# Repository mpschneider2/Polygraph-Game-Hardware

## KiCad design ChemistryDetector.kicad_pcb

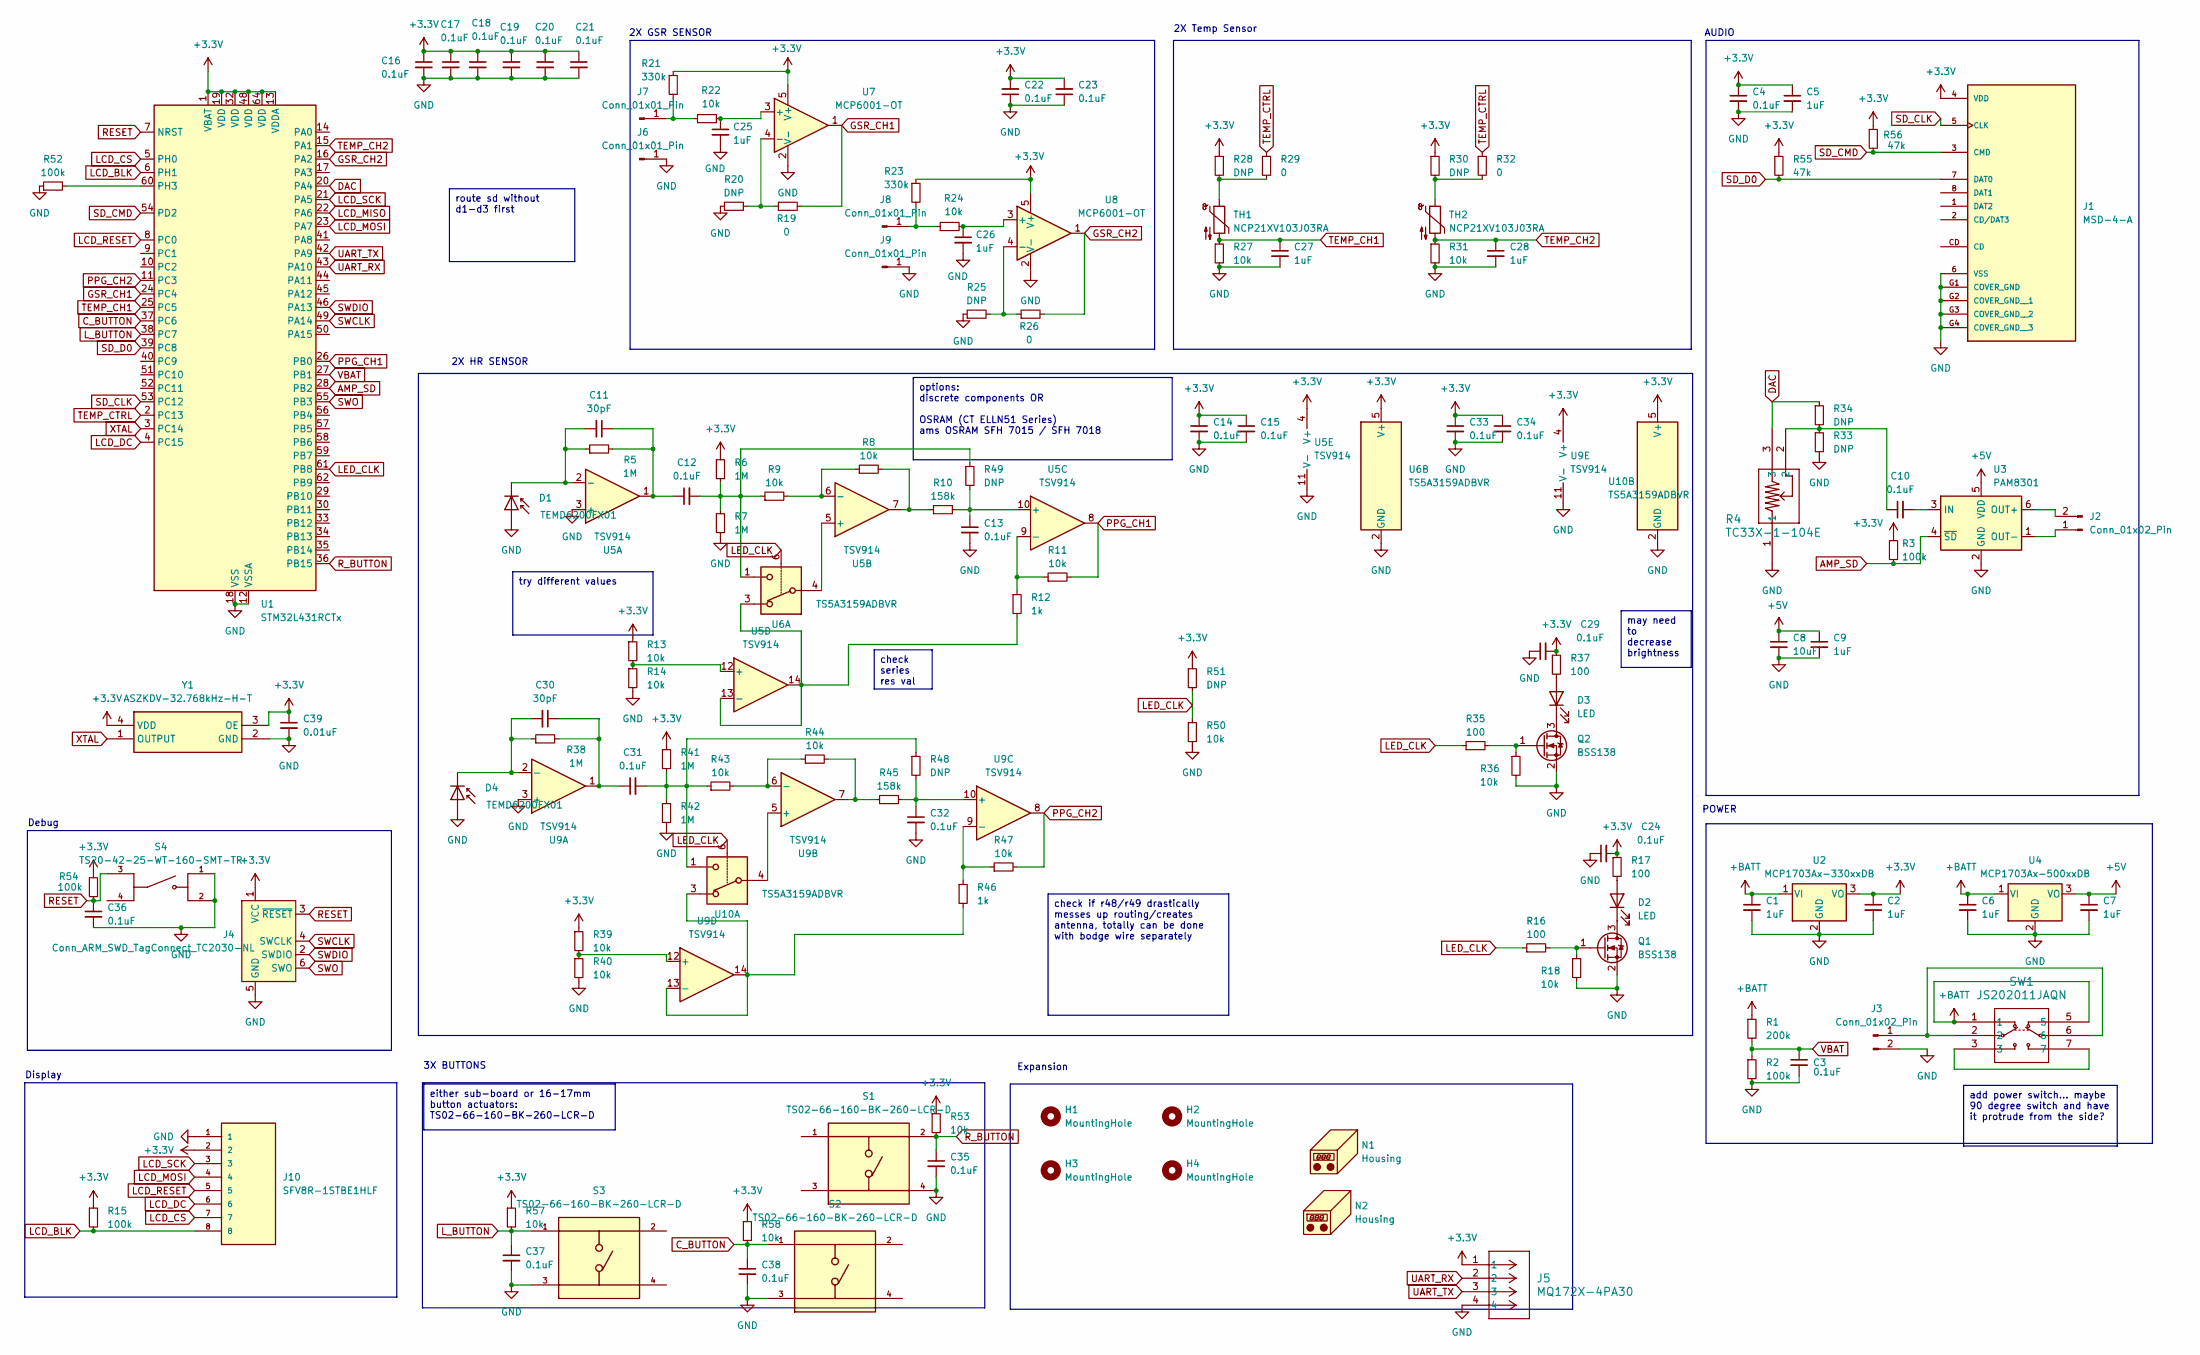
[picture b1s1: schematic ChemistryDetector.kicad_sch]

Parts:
C1, C2, C5, C6, C7, C9, C25, C26, C27, C28: 1uF; C_0603_1608Metric
C3, C4, C10, C12, C13, C14, C15, C16, C17, C18, C19, C20, C21, C22, C23, C24, C29, C31, C32, C33, C34, C35, C36, C37, C38: 0.1uF; C_0603_1608Metric
C8: 10uF; C_0603_1608Metric
C11, C30: 30pF; C_0603_1608Metric
C39: 0.01uF; C_0603_1608Metric
D1, D4: TEMD6200FX01; D_0805_2012Metric
D2, D3: LED; LED_0805_2012Metric
H1, H2, H3, H4: MountingHole; MountingHole_3.2mm_M3
J1: MSD-4-A; CUI_MSD-4-A; PARTREV 1.0
J2: Conn_01x02_Pin; Molex_PicoBlade_53261-0271_1x02-1MP_P1.25mm_Horizontal
J3: Conn_01x02_Pin; PinHeader_1x02_P2.54mm_Vertical
J4: Conn_ARM_SWD_TagConnect_TC2030-NL; Tag-Connect_TC2030-IDC-NL_2x03_P1.27mm_Vertical
J5: MQ172X-4PA30; CONN3_MQ172X-4PA30_HIR
J6, J7, J8, J9: Conn_01x01_Pin; TestPoint_Plated_Hole_D2.0mm
J10: SFV8R-1STBE1HLF; AMPHENOL_SFV8R-1STBE1HLF; PARTREV B
N1, N2: Housing; BLANKPOSITION
Q1, Q2: BSS138; SOT-23
R1: 200k; R_0603_1608Metric
R2, R3, R15, R52, R54: 100k; R_0603_1608Metric
R4: TC33X-1-104E; Potentiometer_Bourns_TC33X_Vertical
R5, R6, R7, R38, R41, R42: 1M; R_0603_1608Metric
R8, R9, R11, R13, R14, R18, R22, R24, R27, R31, R36, R39, R40, R43, R44, R47, R50, R53, R57, R58: 10k; R_0603_1608Metric
R10, R45: 158k; R_0603_1608Metric
R12, R46: 1k; R_0603_1608Metric
R16, R17, R35, R37: 100; R_0603_1608Metric
R19, R26, R29, R32: 0; R_0603_1608Metric
R20, R25, R28, R30, R33, R34, R48, R49, R51: DNP; R_0603_1608Metric
R21, R23: 330k; R_0603_1608Metric
R55, R56: 47k; R_0603_1608Metric
S1, S2, S3: TS02-66-160-BK-260-LCR-D; SW_TS02-66-160-BK-260-LCR-D; PARTREV 1.0
S4: TS20-42-25-WT-160-SMT-TR; SW_TS20-42-25-WT-160-SMT-TR; PARTREV 1.02
SW1: JS202011JAQN; JS202011JAQN_CNK
TH1, TH2: NCP21XV103J03RA; R_0805_2012Metric
U1: STM32L431RCTx; LQFP-64_10x10mm_P0.5mm
U2: MCP1703Ax-330xxDB; SOT-223-3_TabPin2
U3: PAM8301; SOT-23-6
U4: MCP1703Ax-500xxDB; SOT-223-3_TabPin2
U5, U9: TSV914; TSSOP-14_4.4x5mm_P0.65mm
U6, U10: TS5A3159ADBVR; SOT-23-6
U7, U8: MCP6001-OT; SOT-23-5
Y1: ASZKDV-32.768kHz-H-T; ASZKDV32768kHzHT; Manufacturer_Part_Number ASZKDV-32.768kHz-H-T; Mouser Part Number 815-ASZKDV32768KHZHT

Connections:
+3.3V: C2.1, C4.1, C5.1, C14.1, C15.1, C16.1, C17.1, C18.1, C19.1, C20.1, C21.1, C22.2, C23.2, C24.2, C29.2, C33.1, C34.1, C39.1, J1.4 (VDD), J4.1 (VCC), J5.1, J10.2, R3.1, R6.1, R13.1, R15.1, R17.1, R21.1, R23.1, R28.1, R30.1, R37.1, R39.1, R41.1, R51.1, R53.1, R54.1, R55.1, R56.1, R57.1, R58.1, U1.1 (VBAT), U1.13 (VDDA), U1.19 (VDD), U1.32 (VDD), U1.48 (VDD), U1.64 (VDD), U2.3 (VO), U5.4 (V+), U6.5 (V+), U7.5 (V+), U8.5 (V+), U9.4 (V+), U10.5 (V+), Y1.3 (OE), Y1.4 (VDD)
+5V: C7.1, C8.1, C9.1, U3.5 (VDD), U4.3 (VO)
+BATT: C1.1, C6.1, R1.1, SW1.1, SW1.5, U2.1 (VI), U4.1 (VI)
AMP_SD: R3.2, U1.28 (PB2), U3.4 (~SD)
C_BUTTON: C38.1, R58.2, S2.1, U1.37 (PC6)
DAC: R4.3, R34.1, U1.20 (PA4)
GND: C1.2, C2.2, C3.2, C4.2, C5.2, C6.2, C7.2, C8.2, C9.2, C13.2, C14.2, C15.2, C16.2, C17.2, C18.2, C19.2, C20.2, C21.2, C22.1, C23.1, C24.1, C25.2, C26.2, C27.2, C28.2, C29.1, C32.2, C33.2, C34.2, C35.2, C36.2, C37.2, C38.2, C39.2, D1.2 (A), D4.2 (A), J1.6 (VSS), J1.G1 (COVER_GND), J1.G2 (COVER_GND__1), J1.G3 (COVER_GND__2), J1.G4 (COVER_GND__3), J3.2, J4.5 (GND), J5.4, J6.1, J9.1, J10.1, Q1.2 (S), Q2.2 (S), R2.2, R4.1, R7.2, R14.2, R18.2, R20.1, R25.1, R27.2, R31.2, R33.2, R36.2, R40.2, R42.2, R50.2, R52.1, S1.4, S2.3, S3.3, S4.1, S4.2, U1.12 (VSSA), U1.18 (VSS), U1.31 (VSS), U1.47 (VSS), U1.63 (VSS), U2.2 (GND), U3.2 (GND), U4.2 (GND), U5.3 (+), U5.11 (V-), U6.2 (GND), U7.2 (V-), U8.2 (V-), U9.3 (+), U9.11 (V-), U10.2 (GND), Y1.2 (GND)
GSR_CH1: R19.2, U1.24 (PC4), U7.1
GSR_CH2: R26.2, U1.16 (PA2), U8.1
LCD_BLK: J10.8, R15.2, U1.6 (PH1)
LCD_CS: J10.7, U1.5 (PH0)
LCD_DC: J10.6, U1.4 (PC15)
LCD_MISO: U1.22 (PA6)
LCD_MOSI: J10.4, U1.23 (PA7)
LCD_RESET: J10.5, U1.8 (PC0)
LCD_SCK: J10.3, U1.21 (PA5)
LED_CLK: R16.1, R35.1, R50.1, R51.2, U1.61 (PB8), U6.6, U10.6
L_BUTTON: C37.1, R57.2, S3.1, U1.38 (PC7)
unnamed: C10.1, R4.2, R33.1, R34.2
unnamed: C11.1, C12.1, R5.2, U5.1
unnamed: C12.2, R6.2, R7.1, R9.1, R49.1, U6.1
unnamed: C30.1, C31.1, R38.2, U9.1
unnamed: C31.2, R41.2, R42.1, R43.1, R48.1, U10.1
unnamed: C11.2, D1.1 (K), R5.1, U5.2 (-)
unnamed: D2.2 (A), R17.2
unnamed: D2.1 (K), Q1.3 (D)
unnamed: D3.2 (A), R37.2
unnamed: D3.1 (K), Q2.3 (D)
unnamed: C30.2, D4.1 (K), R38.1, U9.2 (-)
unnamed: J2.1, U3.1 (OUT-)
unnamed: J2.2, U3.6 (OUT+)
unnamed: J3.1, SW1.2, SW1.6
unnamed: J7.1, R21.2, R22.1
unnamed: J8.1, R23.2, R24.1
unnamed: Q1.1 (G), R16.2, R18.1
unnamed: Q2.1 (G), R35.2, R36.1
unnamed: R8.2, R10.1, U5.7
unnamed: R28.2, R29.2, TH1.1
unnamed: R30.2, R32.2, TH2.1
unnamed: R44.2, R45.1, U9.7
unnamed: SW1.3, SW1.7
unnamed: R52.2, U1.60 (PH3)
unnamed: C10.2, U3.3 (IN)
unnamed: U5.5 (+), U6.4
unnamed: R8.1, R9.2, U5.6 (-)
unnamed: C13.1, R10.2, R49.2, U5.10 (+)
unnamed: R11.1, R12.1, U5.9 (-)
unnamed: R13.2, R14.1, U5.12 (+)
unnamed: R12.2, U5.13 (-), U5.14, U6.3
unnamed: C25.1, R22.2, U7.3 (+)
unnamed: R19.1, R20.2, U7.4 (-)
unnamed: C26.1, R24.2, U8.3 (+)
unnamed: R25.2, R26.1, U8.4 (-)
unnamed: U9.5 (+), U10.4
unnamed: R43.2, R44.1, U9.6 (-)
unnamed: C32.1, R45.2, R48.2, U9.10 (+)
unnamed: R46.1, R47.1, U9.9 (-)
unnamed: R39.2, R40.1, U9.12 (+)
unnamed: R46.2, U9.13 (-), U9.14, U10.3
PPG_CH1: R11.2, U1.26 (PB0), U5.8
PPG_CH2: R47.2, U1.11 (PC3), U9.8
RESET: C36.1, J4.3 (~RESET), R54.2, S4.3, U1.7 (NRST)
R_BUTTON: C35.1, R53.2, S1.2, U1.36 (PB15)
SD_CLK: J1.5 (CLK), U1.53 (PC12)
SD_CMD: J1.3 (CMD), R56.2, U1.54 (PD2)
SD_D0: J1.7 (DAT0), R55.2, U1.39 (PC8)
SWCLK: J4.4 (SWCLK), U1.49 (PA14)
SWDIO: J4.2 (SWDIO), U1.46 (PA13)
SWO: J4.6 (SWO), U1.55 (PB3)
TEMP_CH1: C27.1, R27.1, TH1.2, U1.25 (PC5)
TEMP_CH2: C28.1, R31.1, TH2.2, U1.15 (PA1)
TEMP_CTRL: R29.1, R32.1, U1.2 (PC13)
UART_RX: J5.2, U1.43 (PA10)
UART_TX: J5.3, U1.42 (PA9)
VBAT: C3.1, R1.2, R2.1, U1.27 (PB1)
XTAL: U1.3 (PC14), Y1.1 (OUTPUT)

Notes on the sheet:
check series res val
route sd without d1-d3 first
try different values
may need to decrease brightness
check if r48/r49 drastically messes up routing/creates antenna, totally can be done with bodge wire separately
options: discrete components OR OSRAM (CT ELLN51 Series) ams OSRAM SFH 7015 / SFH 7018
either sub-board or 16-17mm button actuators: TS02-66-160-BK-260-LCR-D
add power switch... maybe 90 degree switch and have it protrude from the side?
Display
2X HR SENSOR
2X GSR SENSOR
Expansion
2X Temp Sensor
3X BUTTONS
AUDIO
Debug
POWER

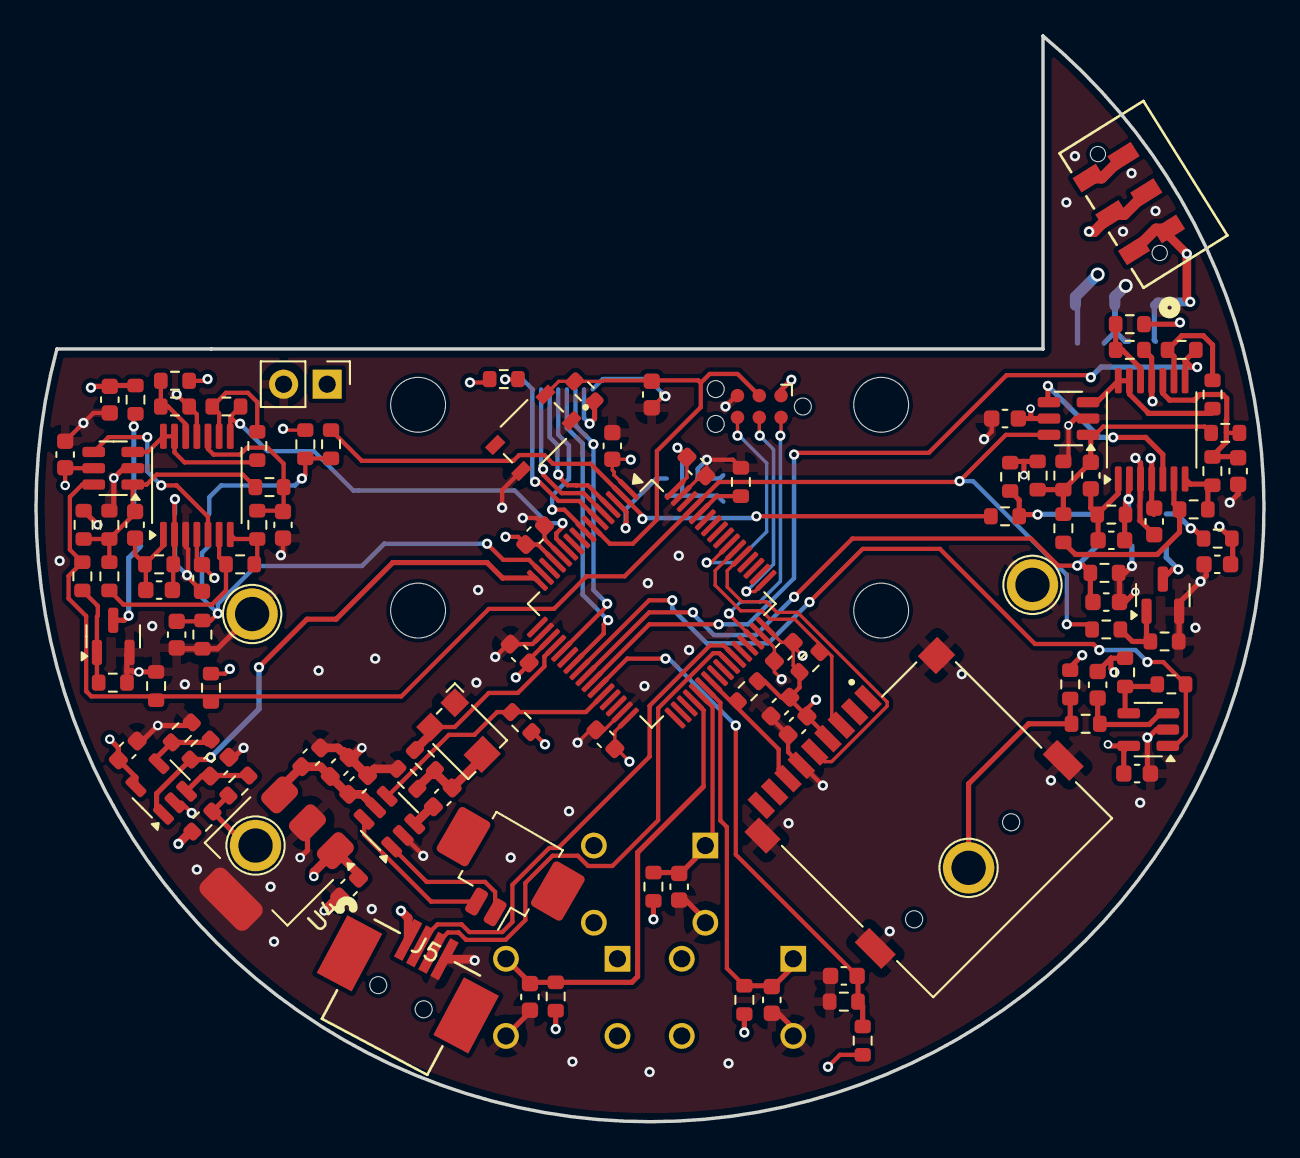
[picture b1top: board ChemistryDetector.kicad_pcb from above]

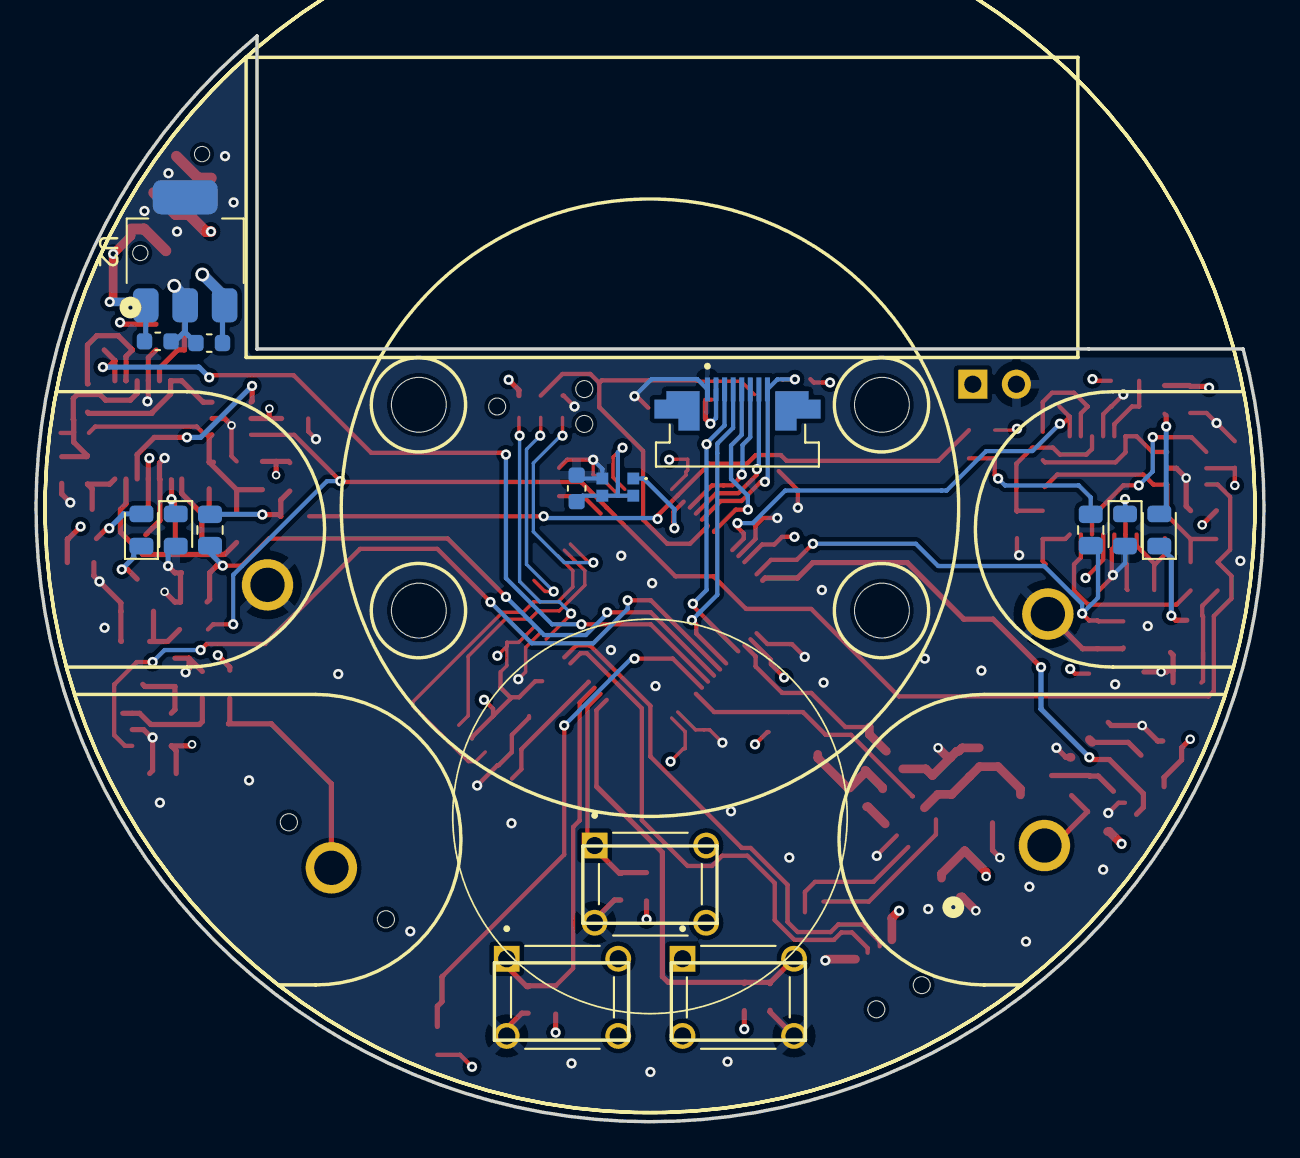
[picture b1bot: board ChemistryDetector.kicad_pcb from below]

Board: 4 copper layers, 71.6 x 63.3 mm, 137 parts (17 on the bottom side), 75 nets.
